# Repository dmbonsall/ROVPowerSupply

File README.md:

<h1>ROV Power Supply</h1>
<h2>A 1400W DC/DC converter for use with underwater Remotly Operated Vehicals (ROV)</h2>
<p>This power supply was designed to convert 48VDC to 12VDC and 5VDC for use in the MATE ROV competionion. It uses multiple DC/DC converters from Murata Power to perform the power conversions.</p>
<p>There are two versions of this power supply. The first supply is a simple version which only includes the converter modules and a handful of passives. The second version is a "smart" version which includes an arduino pro mini that interacts with the converter modules to monitor the state and power output of the 12V power modules.</p>
<p>Unfortunatly our team lost funding before this could be manufactured, however the hardware design is complete and has been successfully passed a design/electrical rule check provided by Texas A&M University. A BOM for each version is provided with manufacturer and vendor part numbers.</p>

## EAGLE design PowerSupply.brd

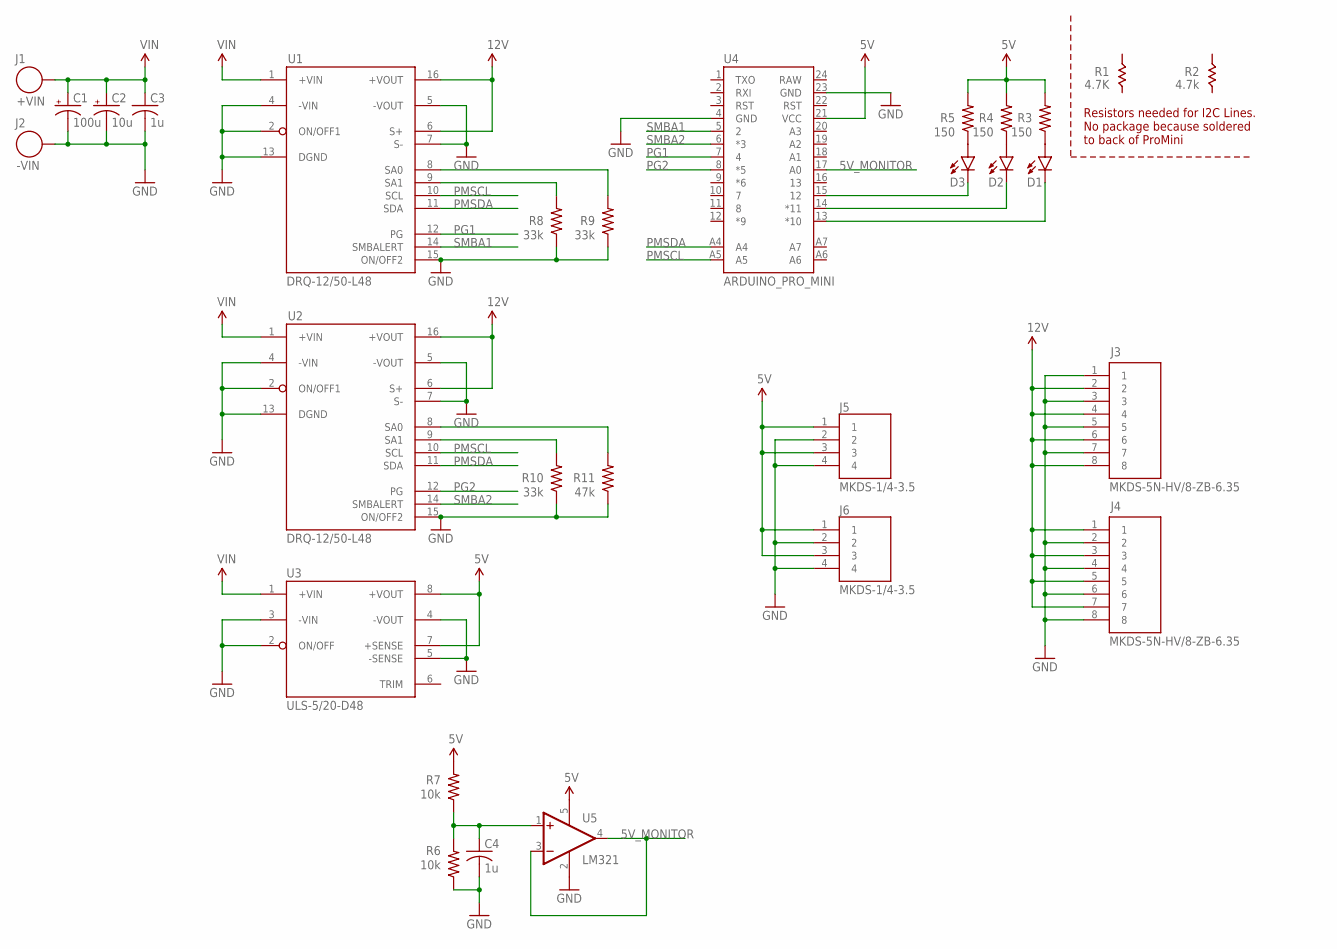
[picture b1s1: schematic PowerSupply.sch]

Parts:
C1: 100u; PANASONIC_E
C2: 10u; PANASONIC_D
C3, C4: 1u; C0603
D1, D2, D3: LED1206; LED-1206
J1: +VIN; 10AWG
J2: -VIN; 10AWG
J3, J4: MKDS-5N-HV/8-ZB-6.35; 1777600
J5, J6: MKDS-1/4-3.5; 1751264
R3, R4, R5: 150; 0603-RES
R6, R7: 10k; 0603-RES
R8, R9, R10: 33k; 0603-RES
R11: 47k; 0603-RES
U1, U2: DRQ-12/50-L48; ABC(PMBUS)
U3: ULS-5/20-D48; 1/16_BRICK_THROUGH_HOLE
U4: ARDUINO_PRO_MINI
U5: LM321; SOT23-5

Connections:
5V: J5.1, J5.3, J6.1, J6.3, R3.2, R4.2, R5.2, R7.2, U3.7 (+SENSE), U3.8 (+VOUT), U4.21 (VCC), U5.5 (V+)
5V_MONITOR: U4.17 (A0), U5.3 (-IN), U5.4 (OUT)
12V: J3.2, J3.4, J3.6, J3.8, J4.1, J4.3, J4.5, J4.7, U1.6 (S+), U1.16 (+VOUT), U2.6 (S+), U2.16 (+VOUT)
GND: C1.-, C2.-, C3.2, C4.2, J2.P$1, J3.1, J3.3, J3.5, J3.7, J4.2, J4.4, J4.6, J4.8, J5.2, J5.4, J6.2, J6.4, R6.1, R8.1, R9.1, R10.1, R11.1, U1.2 (ON/OFF1), U1.4 (-VIN), U1.5 (-VOUT), U1.7 (S-), U1.13 (DGND), U1.15 (ON/OFF2), U2.2 (ON/OFF1), U2.4 (-VIN), U2.5 (-VOUT), U2.7 (S-), U2.13 (DGND), U2.15 (ON/OFF2), U3.2 (ON/OFF), U3.3 (-VIN), U3.4 (-VOUT), U3.5 (-SENSE), U4.4 (GND), U4.23 (GND), U5.2 (V-)
unnamed: R10.2, U2.9 (SA1)
unnamed: C4.1, R6.2, R7.1, U5.1 (+IN)
unnamed: R11.2, U2.8 (SA0)
unnamed: R8.2, U1.9 (SA1)
unnamed: R9.2, U1.8 (SA0)
unnamed: D3.C, U4.15 (12)
unnamed: D2.C, U4.14 (*11)
unnamed: D1.C, U4.13 (*10)
unnamed: D1.A, R3.1
unnamed: D2.A, R4.1
unnamed: D3.A, R5.1
PG1: U1.12 (PG), U4.7 (4)
PG2: U2.12 (PG), U4.8 (*5)
PMSCL: U1.10 (SCL), U2.10 (SCL), U4.A5
PMSDA: U1.11 (SDA), U2.11 (SDA), U4.A4
SMBA1: U1.14 (SMBALERT), U4.5 (2)
SMBA2: U2.14 (SMBALERT), U4.6 (*3)
VIN: C1.+, C2.+, C3.1, J1.P$1, U1.1 (+VIN), U2.1 (+VIN), U3.1 (+VIN)

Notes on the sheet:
Resistors needed for I2C Lines. No package because soldered to back of ProMini

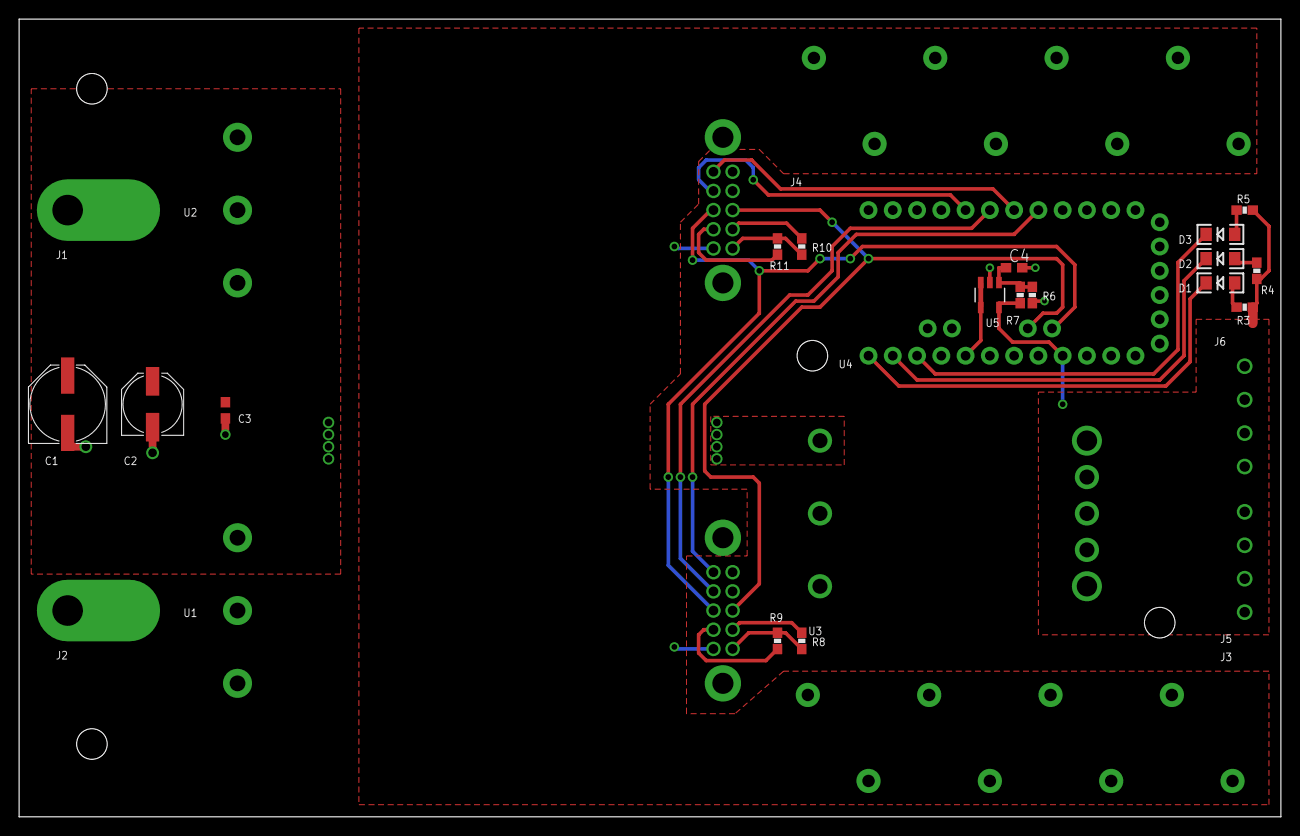
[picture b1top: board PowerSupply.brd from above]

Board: 2 copper layers, 132.1 x 83.5 mm, 27 parts (0 on the bottom side), 22 nets.

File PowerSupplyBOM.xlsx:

Part No. | Manufacturer Part No. | Vendor | Vendor Part No. | Price | Qty | Description | Totals
U1, U2 | DRQ-12/50-L48NKSA-C | Digikey | 811-3046-ND | 100.15 | 2 | 12VDC Converter | 200.3
U3 | ULS-5/20-D48N-C | Digikey | 811-2789-ND | 36.72 | 1 | 5VDC Converter | 36.72
U4 | Arduino Pro Mini 5V | Sparkfun | DEV-11113 | 9.99 | 1 | Microcontroller Breakout | 9.99
U5 | LM321MF/NOPB | Digikey | LM321MF/NOPBCT-ND | 0.67 | 1 | Op amp | 0.67
R1, R2 | RC0603FR-074K7L | Digikey | 311-4.70KHRCT-ND | 0.1 | 2 | 4.7kohm resitor | 0.2
R3 - R5 | RC0603FR-07150RL | Digikey | 311-150HRCT-ND | 0.1 | 3 | 150ohm Resistor | 0.30000000000000004
R6 - R7 | RC0603FR-0710KL | Digikey | 311-10.0KHRCT-ND | 0.1 | 2 | 10kohm Resistor | 0.2
R8 - R10 | RC0603FR-0733KL | Digikey | 311-33.0KHRCT-ND | 0.1 | 3 | 33kohm Resistor | 0.30000000000000004
R11 | RC0603FR-0747KL | Digikey | 311-47.0KHRCT-ND | 0.1 | 1 | 47kohm Resistor | 0.1
D1 - D3 | 150120RS75000 | Digikey | 732-4991-1-ND | 0.34 | 3 | LED, Red | 1.02
C1 | EEV-FK1K101Q | Digikey | PCE3493CT-ND | 1.28 | 1 | 100u Cap | 1.28
C2 | EEE-FK1K100XP | Digikey | PCE3827CT-ND | 0.6 | 1 | 10u Cap | 0.6
C3, C4 | CC0603KRX7R0BB102 | Digikey | 311-1467-1-ND | 0.1 | 2 | 1u Cap | 0.2
J3 - J4 | 1777600 | Digikey | 277-9763-ND | 7.95 | 2 | 12V Terminals | 15.9
J5 - J6 | 1751264 | Digikey | 277-5744-ND | 2.2799999999999998 | 2 | 5V Terminals | 4.5599999999999996
n/a | Break Away Headers | Sparkfun | PRT-00116 | 1.5 | 4 | Headers | 6
 |  |  |  |  |  |  | 278.33999999999997

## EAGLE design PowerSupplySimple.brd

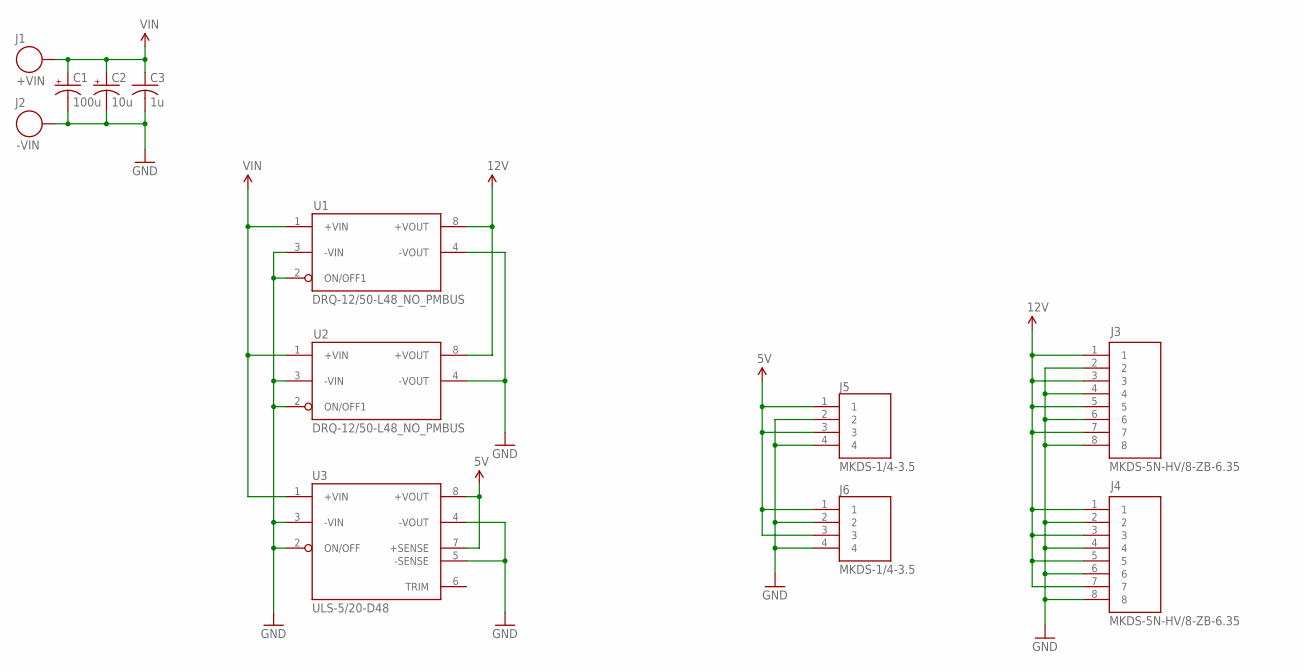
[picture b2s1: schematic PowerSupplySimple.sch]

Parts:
C1: 100u; PANASONIC_E
C2: 10u; PANASONIC_E
C3: 1u; C0603
J1: +VIN; 10AWG
J2: -VIN; 10AWG
J3, J4: MKDS-5N-HV/8-ZB-6.35; 1777600
J5, J6: MKDS-1/4-3.5; 1751264
U1, U2: DRQ-12/50-L48_NO_PMBUS; DRQ(NO_PMBUS)
U3: ULS-5/20-D48; 1/16_BRICK_THROUGH_HOLE

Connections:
5V: J5.1, J5.3, J6.1, J6.3, U3.7 (+SENSE), U3.8 (+VOUT)
12V: J3.1, J3.3, J3.5, J3.7, J4.1, J4.3, J4.5, J4.7, U1.8 (+VOUT), U2.8 (+VOUT)
GND: C1.-, C2.-, C3.2, J2.P$1, J3.2, J3.4, J3.6, J3.8, J4.2, J4.4, J4.6, J4.8, J5.2, J5.4, J6.2, J6.4, U1.2 (ON/OFF1), U1.3 (-VIN), U1.4 (-VOUT), U2.2 (ON/OFF1), U2.3 (-VIN), U2.4 (-VOUT), U3.2 (ON/OFF), U3.3 (-VIN), U3.4 (-VOUT), U3.5 (-SENSE)
VIN: C1.+, C2.+, C3.1, J1.P$1, U1.1 (+VIN), U2.1 (+VIN), U3.1 (+VIN)

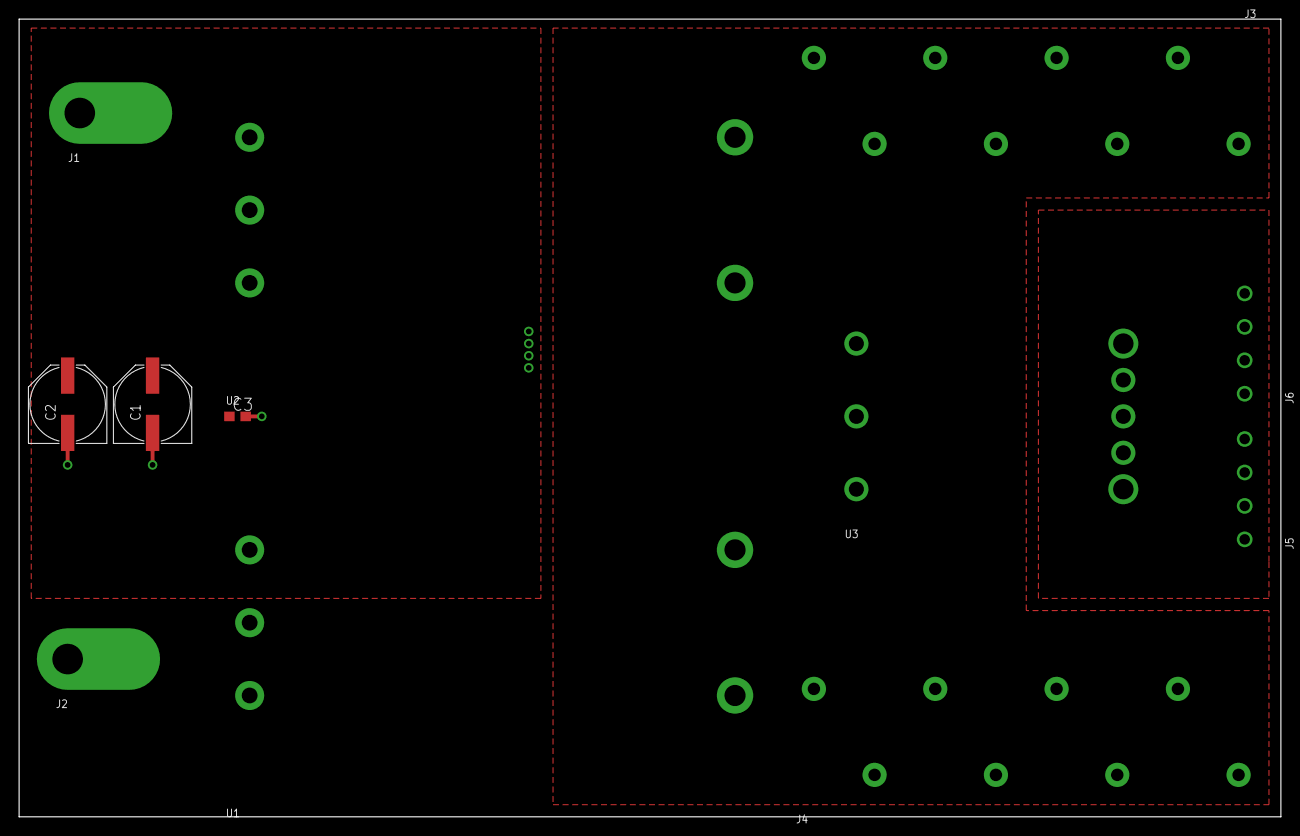
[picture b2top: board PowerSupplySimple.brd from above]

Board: 2 copper layers, 132.1 x 83.5 mm, 12 parts (0 on the bottom side), 4 nets.

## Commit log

2018-04-30 Initial commit, added all of the hardware files and bom's
2018-04-30 Added .gitignore
2018-04-30 Added simple README, needs work to make it more detailed and complete
2018-04-30 Added close tags to README so that it will render propperly on github

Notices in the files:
parts and their libraries:
SparkFun-LED: Licensing: Creative Commons ShareAlike 4.0 International - https://creativecommons.org/licenses/by-sa/4.0
